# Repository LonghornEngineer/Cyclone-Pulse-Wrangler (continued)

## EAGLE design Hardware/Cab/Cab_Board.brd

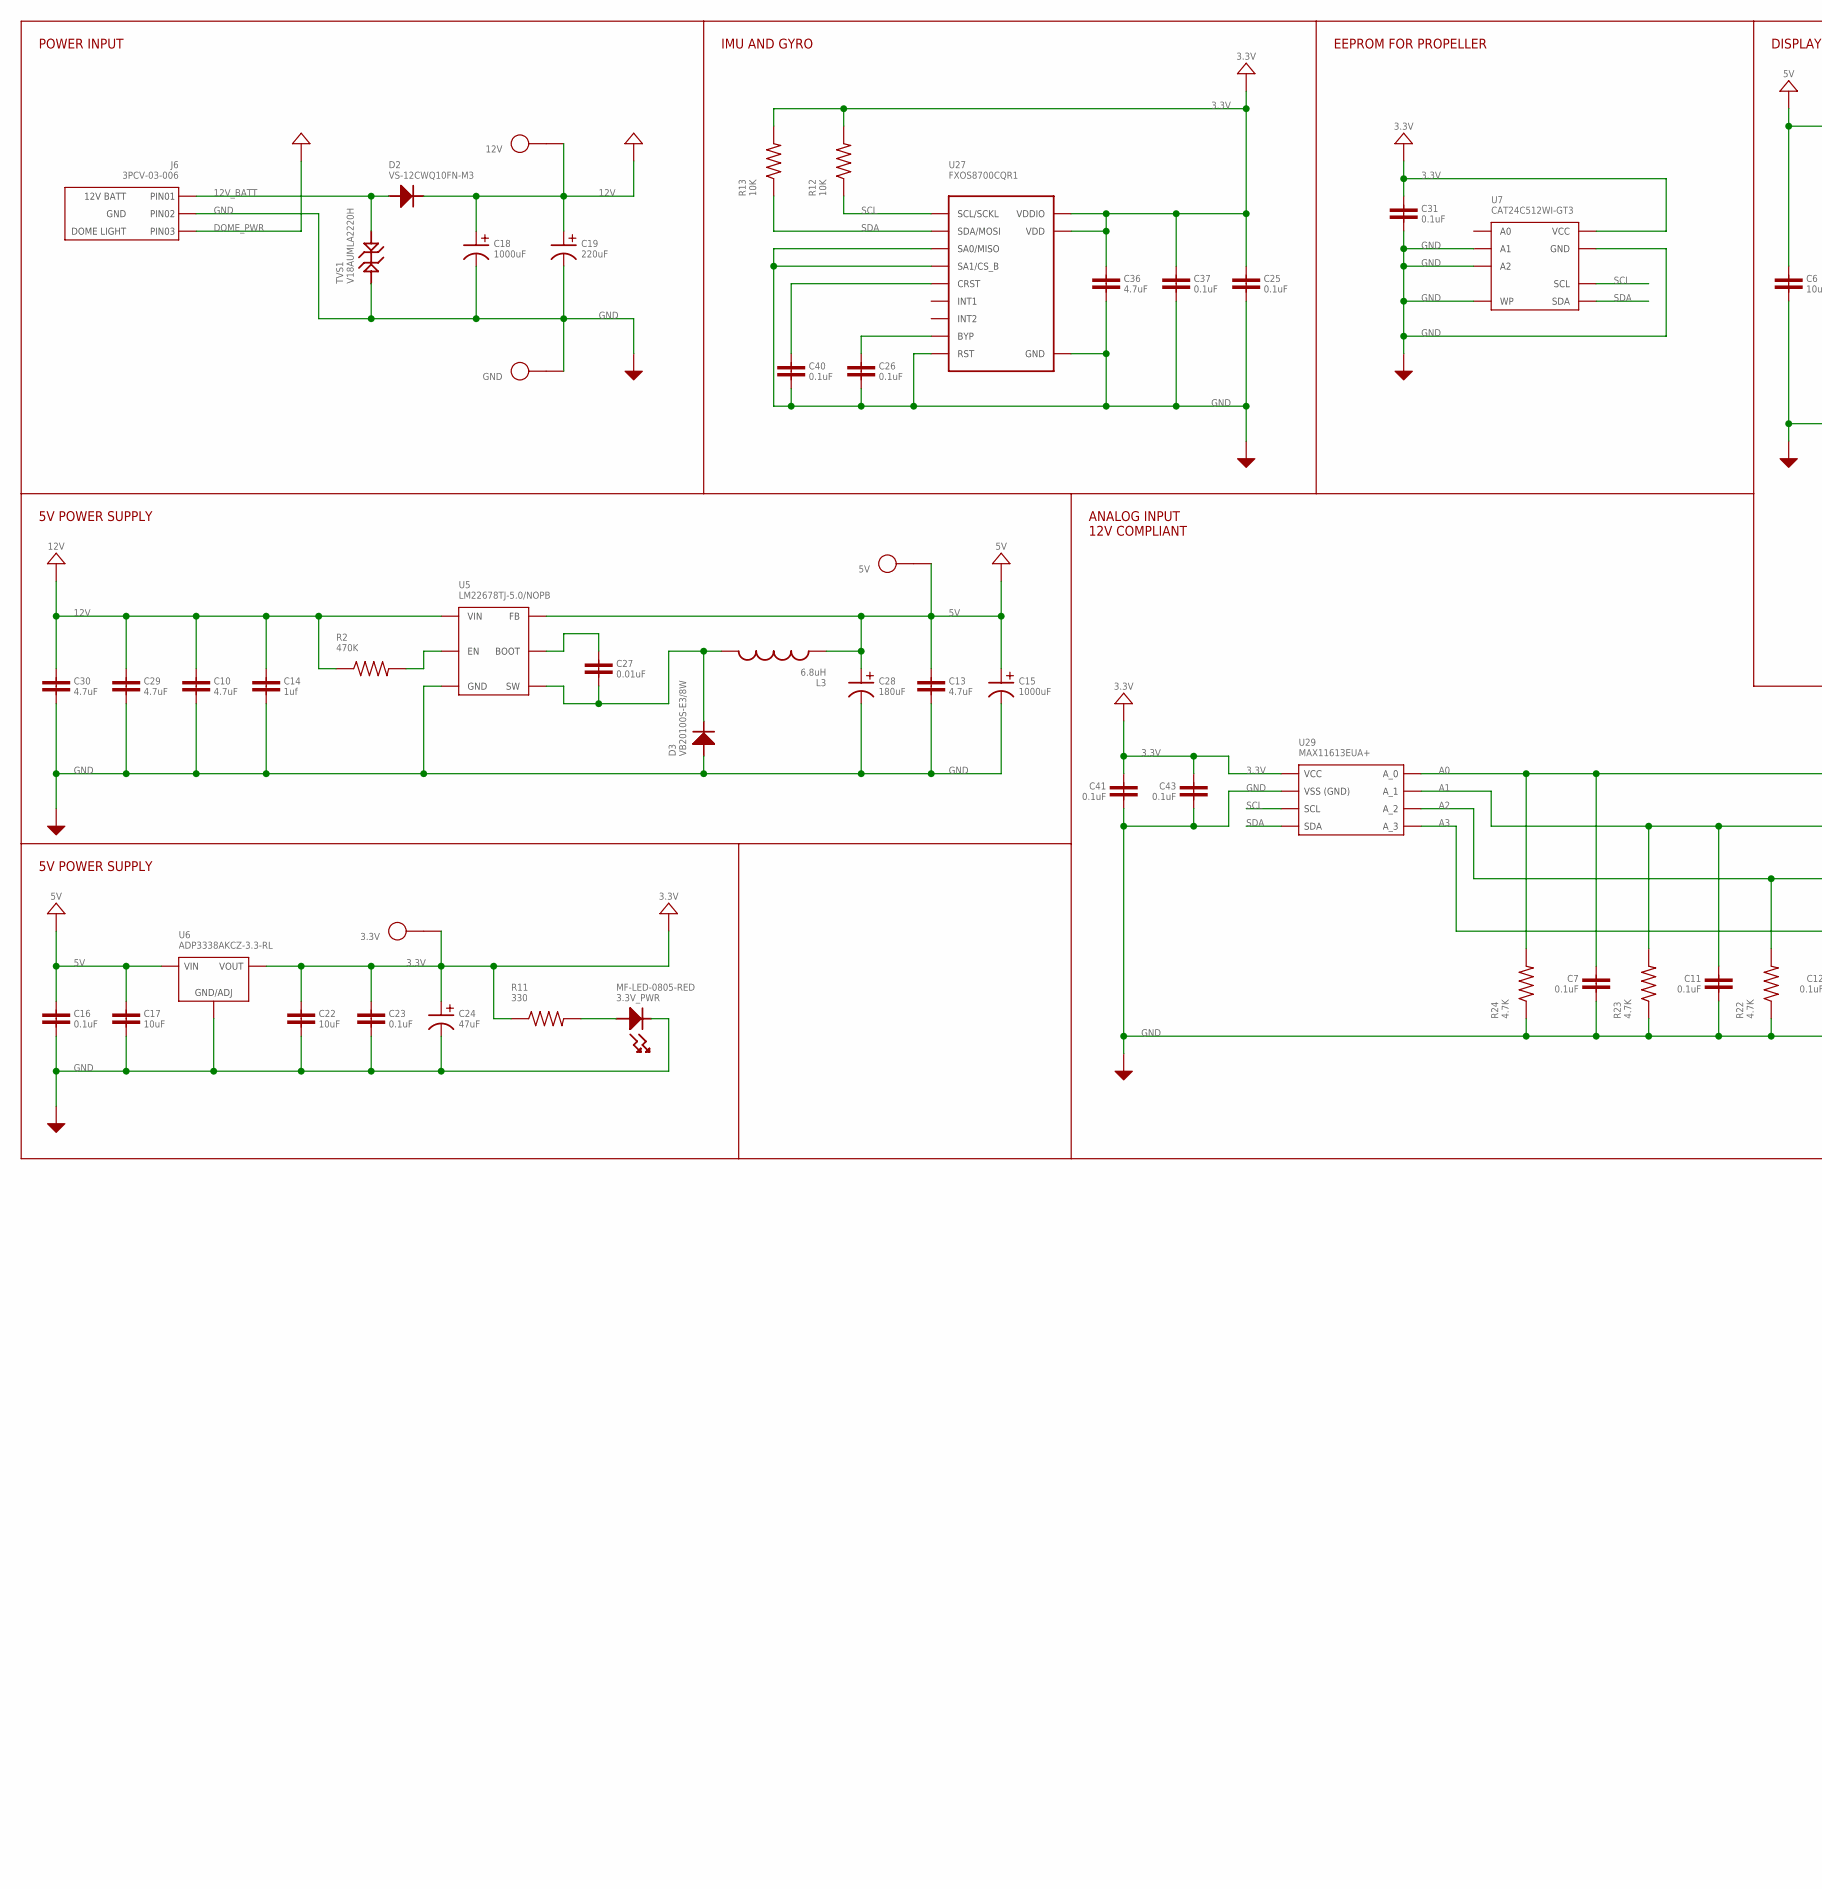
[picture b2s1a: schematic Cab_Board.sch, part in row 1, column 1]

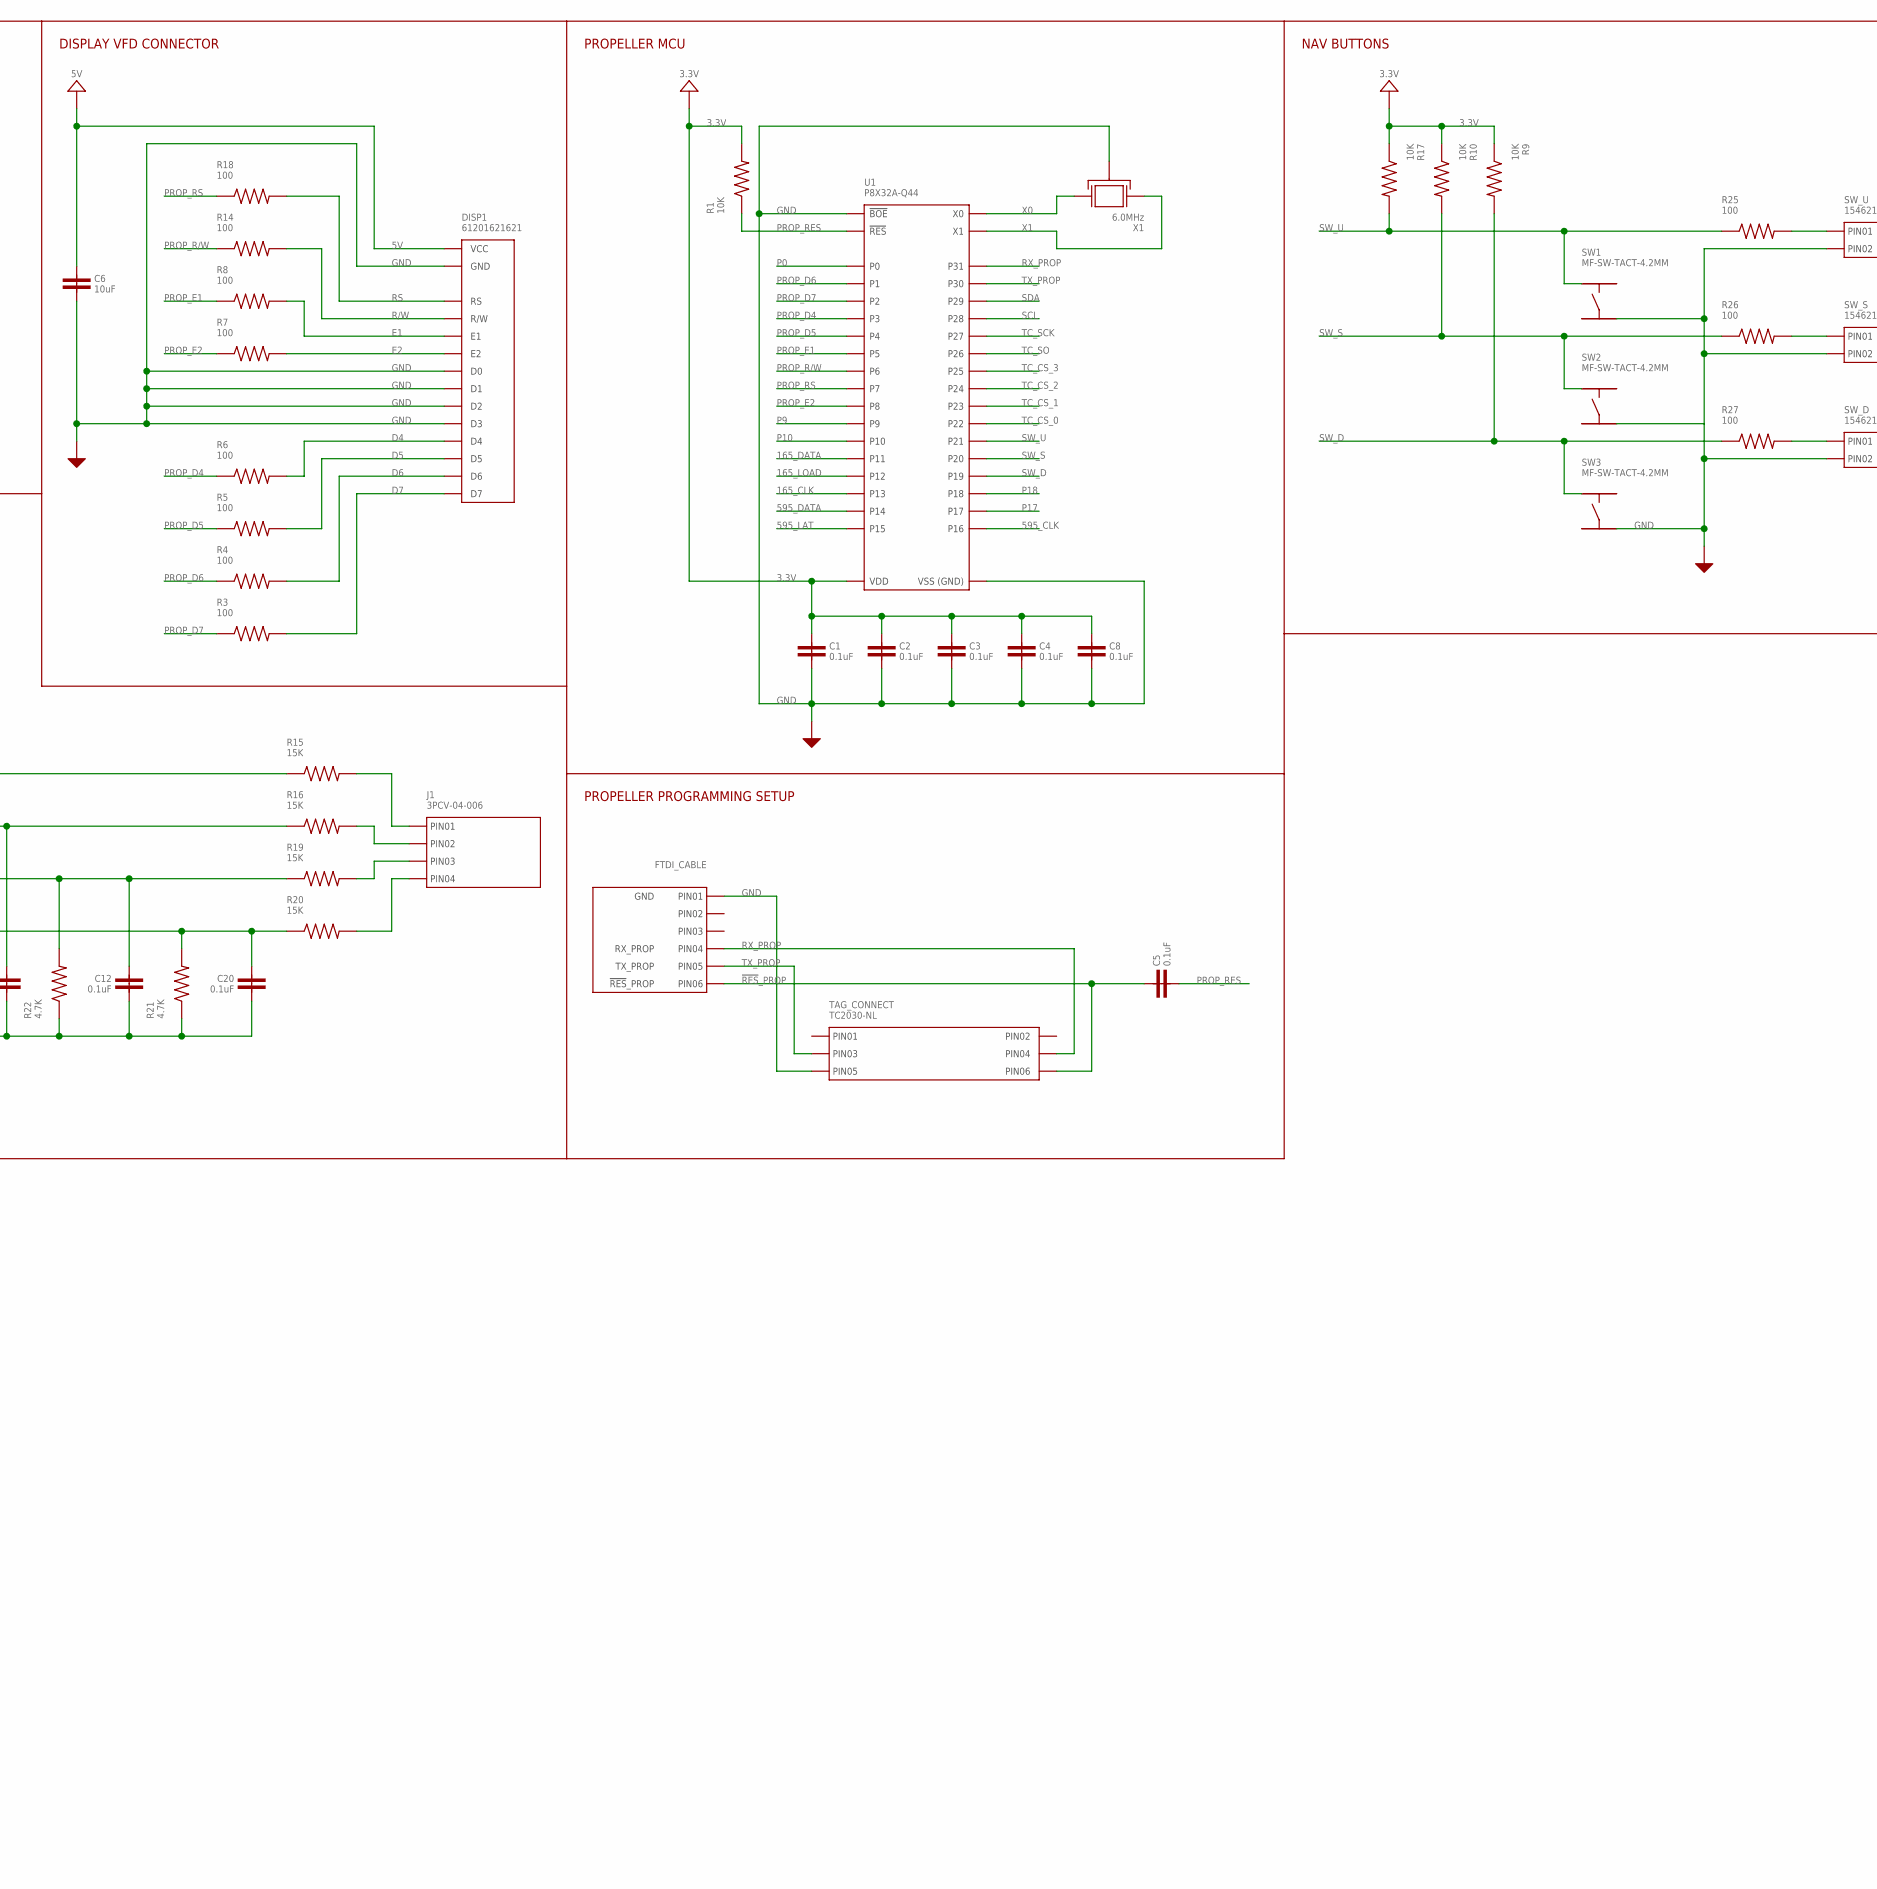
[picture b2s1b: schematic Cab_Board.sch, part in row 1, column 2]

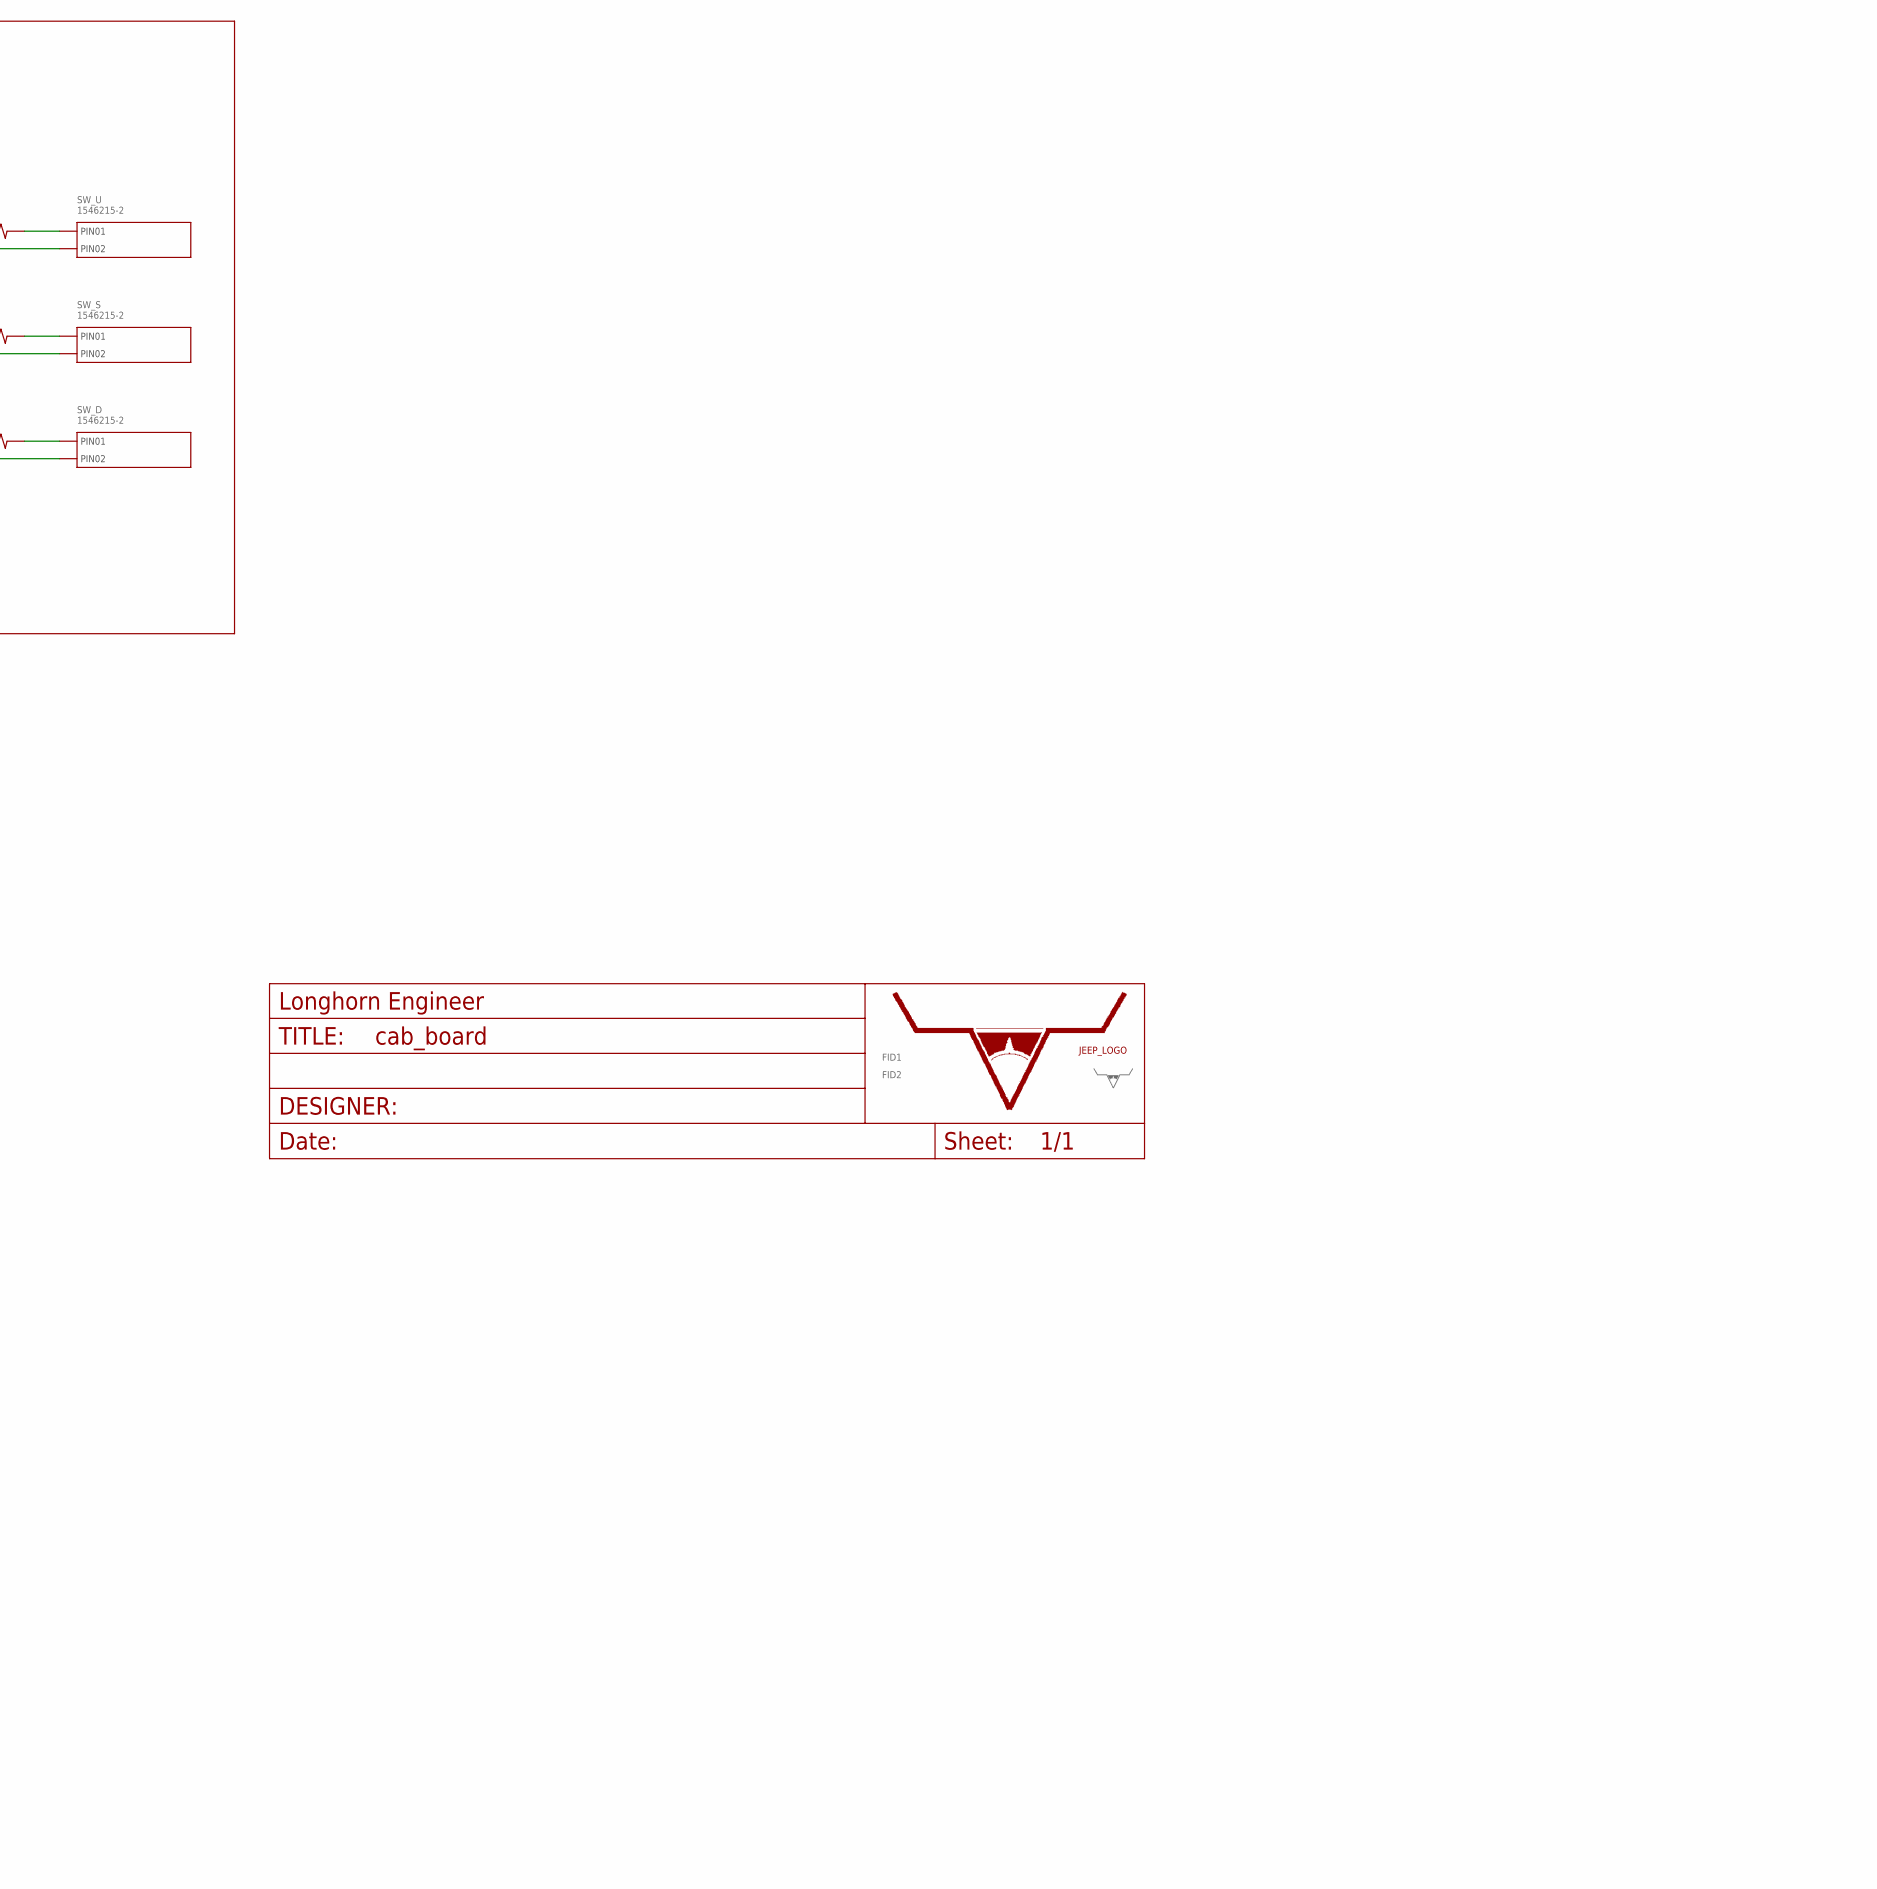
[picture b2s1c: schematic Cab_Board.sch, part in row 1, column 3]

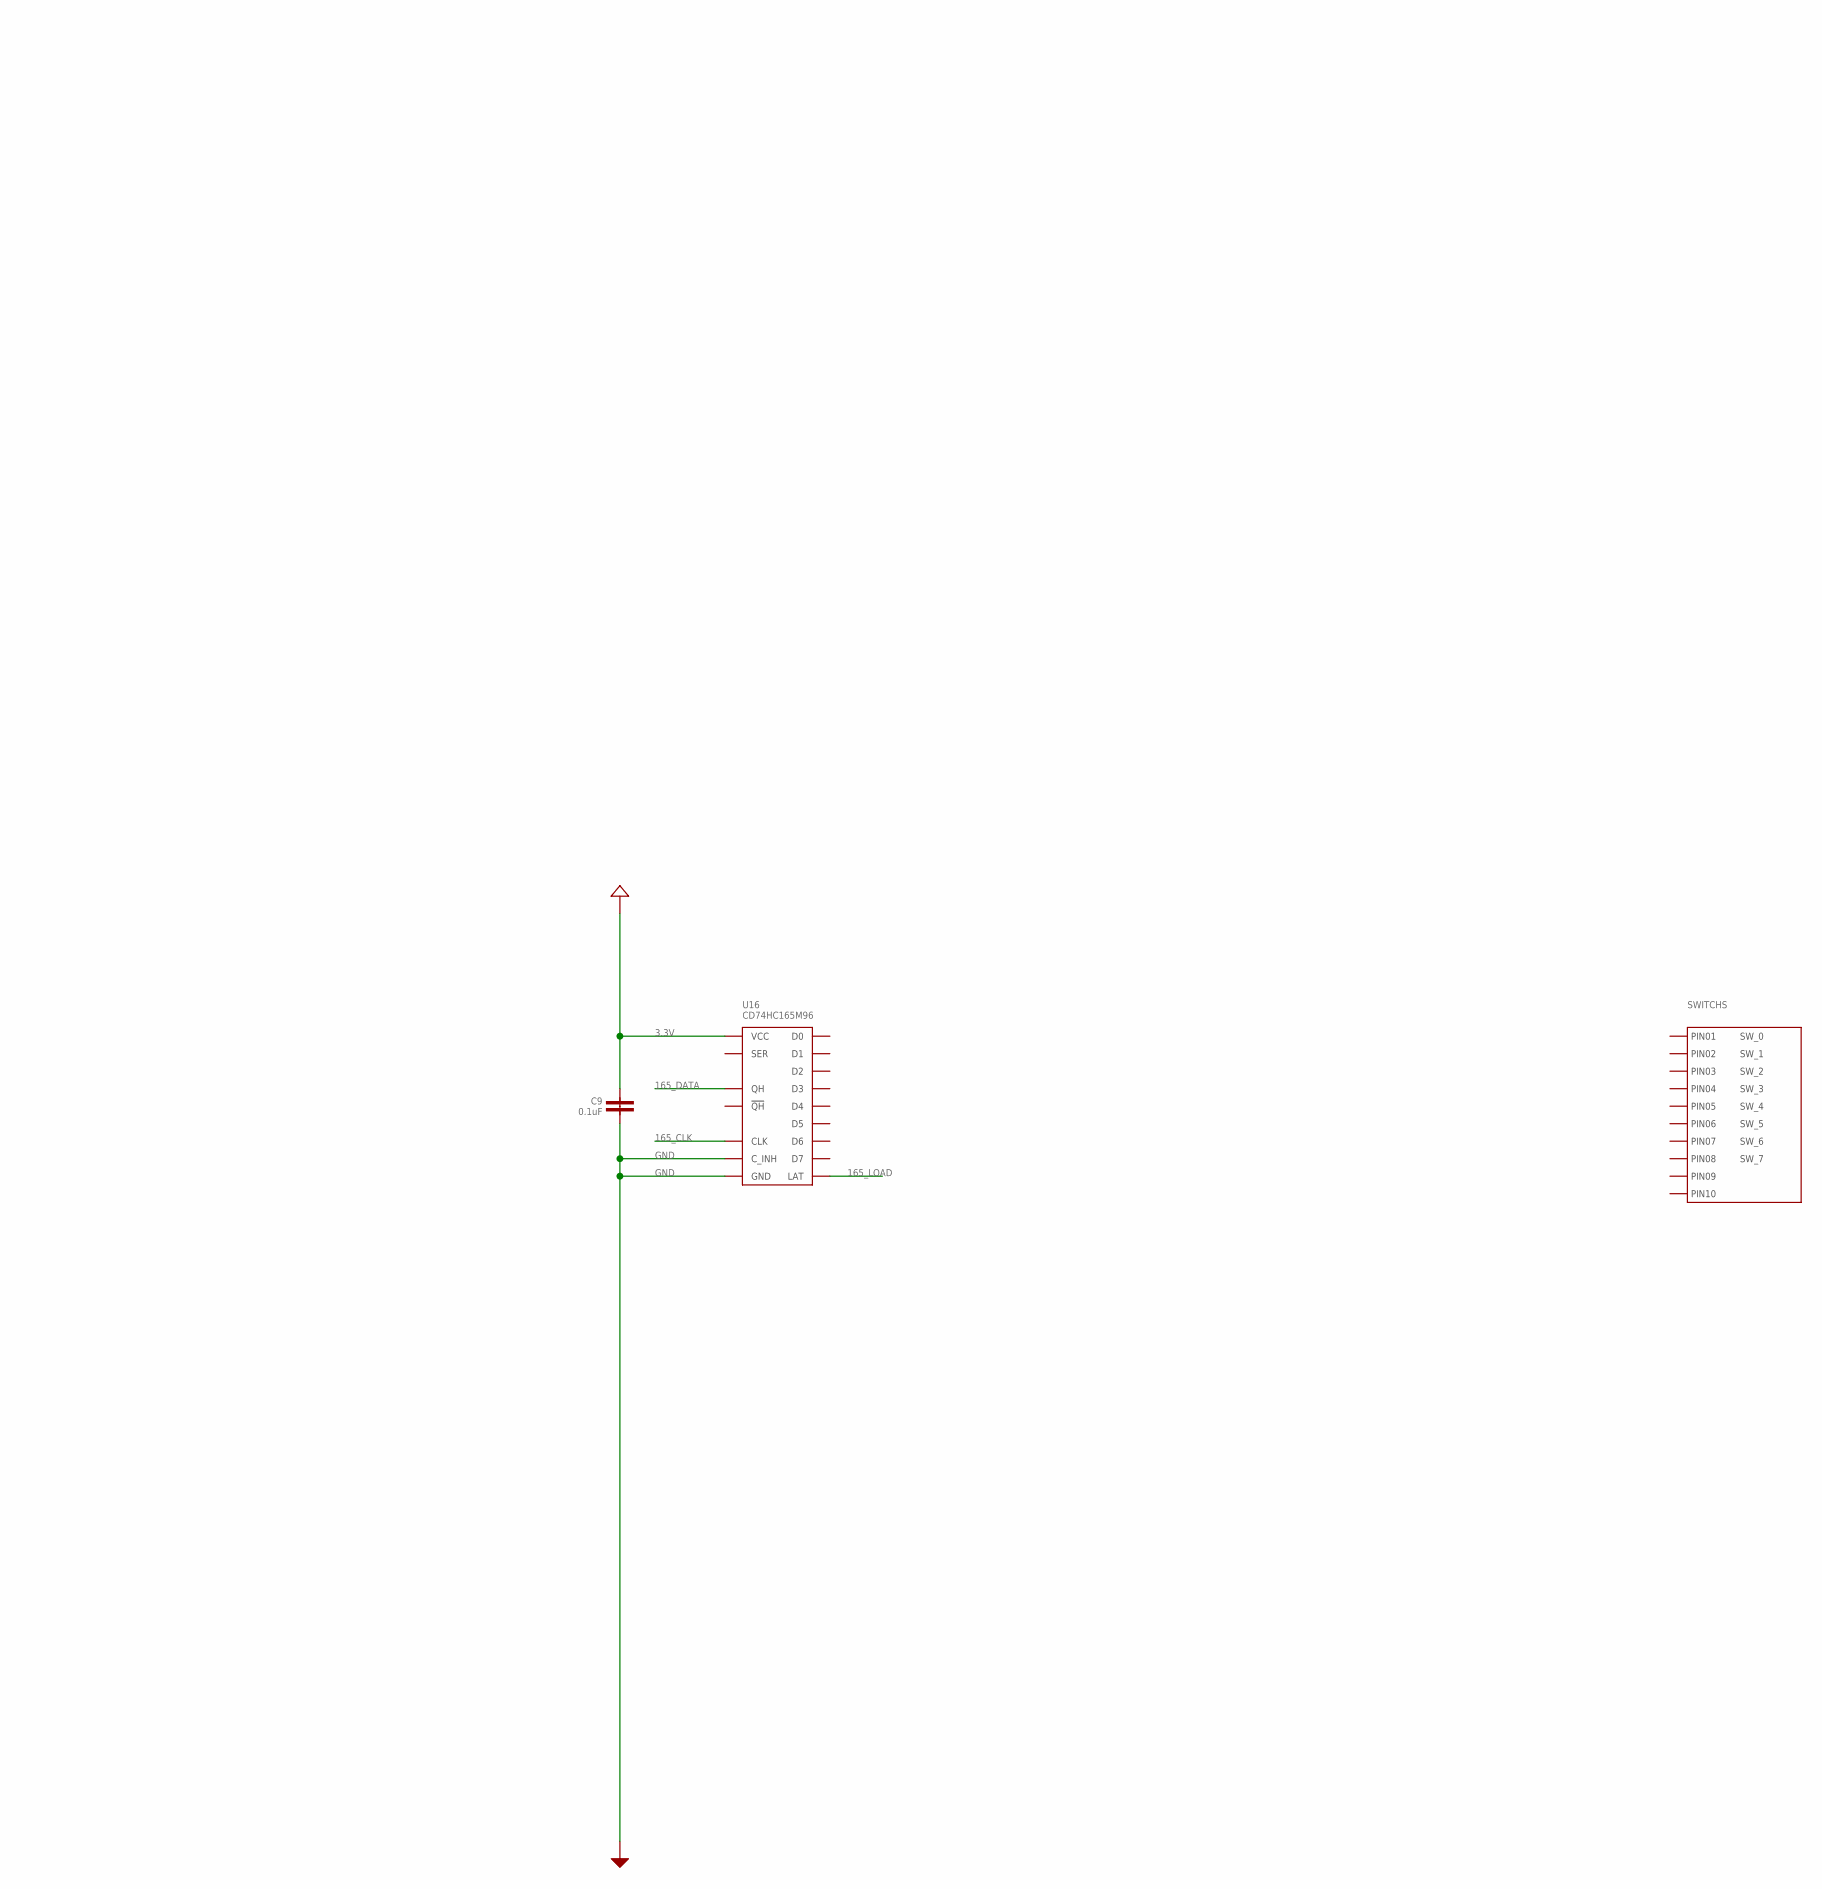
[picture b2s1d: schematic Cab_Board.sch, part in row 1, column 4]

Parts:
3.3V: TEST_POINT_SINGLE_KEYSTONE_5115-5119; KEYSTONE_5115-5119
3.3V_PWR: MF-LED-0805-RED; LED_0805; MPN MF-LED-0805-RED
5V, 12V: TEST_POINT_SINGLE_KEYSTONE_5115-5119; KEYSTONE_5115-5119; MPN 5115
C1, C2, C3, C4, C7, C8, C11, C12, C16, C20, C23, C25, C26, C31, C37, C40, C41, C43: 0.1uF; 0805; MPN MF-CAP-0805-0.1uF
C5: 0.1uF; 0603; MPN MF-CAP-0805-0.1uF
C6, C17: 10uF; 1206; MPN MF-CAP-1206-10uF
C9: 0.1uF; 0805
C10, C13, C29, C30: 4.7uF; 1210; MPN GRJ32DC72A475KE11L
C14: 1uf; 0805; MPN C0805C105K5RACTU
C15: 1000uF; 10MM_CAP_SMD; MPN UWZ1A102MCL1GS
C18: 1000uF; 12.5MM_CAP_PTH; MPN UBW1H102MHD
C19: 220uF; 10MM_CAP_SMD; MPN UWZ1H221MCL1GS
C22: 10uF; 1210; MPN MF-CAP-1206-10uF
C24: 47uF; 6.3MM_CAP_SMD; MPN UWJ1C470MCL1GB
C27: 0.01uF; 0805; MPN C0805C103K5RACTU
C28: 180uF; 8MM_CAP_SMD; MPN 16SVP180M
C36: 4.7uF; 1206; MPN GRJ32DC72A475KE11L
D2: VS-12CWQ10FN-M3; D-PAK(TO-252AA); MPN VS-12CWQ10FN-M3
D3: VB20100S-E3/8W; D2PAK(TO-263AB)
DISP1: 61201621621; CU40045-UW1J; MPN 61201621621
FID1, FID2: FIDUCIAL_0.5MM
FTDI_CABLE: CON_01X06_2.54MM_PIN_HEADER; 2.54MM_01X06_PIN_HEADER
GND: TEST_POINT_SINGLE_KEYSTONE_5115-5119; KEYSTONE_5115-5119; MPN 5115
J1: 3PCV-04-006; MPN 3PCV-04-006
J6: 3PCV-03-006; MPN 3PCV-03-006
L3: 6.8uH; IHLP-5050; MPN IHLP5050CEER6R8M01
R1: 10K; 0805
R2: 470K; 0603; MPN MF-RES-0603-470K
R3, R4, R5, R6, R7, R8, R14, R18, R25, R26, R27: 100; 0603; MPN MF-RES-0603-100
R9, R10, R12, R13, R17: 10K; 0603; MPN MF-RES-0603-10K
R11: 330; 0603; MPN MF-RES-0603-330
R15, R16, R19, R20: 15K; 0603; MPN MF-RES-0603-15K
R21, R22, R23, R24: 4.7K; 0603; MPN MF-RES-0603-4.7K
SW1, SW2, SW3: MF-SW-TACT-4.2MM; TACT4.2MM
SWITCHS: CON_01X10_1-282834-0; 1-282834-0
SW_D: 1546215-2; MPN 1546215-2
SW_S: 1546215-2; MPN 1546215-2
SW_U: 1546215-2; MPN 1546215-2
TAG_CONNECT: TC2030-NL; TC2030
TVS1: V18AUMLA2220H; 2220
U1: P8X32A-Q44; LQFP44
U5: LM22678TJ-5.0/NOPB; LM22678_TO-263-EP-7; MPN LM22678TJ-5.0/NOPB
U6: ADP3338AKCZ-3.3-RL; ADP3338_SOT-223-3; MPN ADP3338AKCZ-3.3-RL
U7: CAT24C512WI-GT3; SOIC-8_W; MPN CAT24C512WI-GT3
U16: CD74HC165M96; CD74HC165_SOIC-16
U27: FXOS8700CQR1; MPN FXOS8700CQR1
U29: MAX11613EUA+; MAX11613_UMAX-8; MPN MAX11613EUA+
U$1: LHE_FRAME
U$35: JEEP_LOGO_SILK_MEDIUM; JEEP_SILK_MEDIUM
U$42: LHE_LOGOLHE_LOGO; LHE_LOGO
X1: 6.0MHz; 7MMX5MM; MPN ABMM-6.000MHZ-B2-T

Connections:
3.3V: 3.3V.P$1, C1.1, C2.1, C3.1, C4.1, C8.1, C9.1, C22.1, C23.1, C24.POS, C25.1, C31.1, C36.1, C37.1, C41.1, C43.1, R1.2, R9.1, R10.1, R11.1, R12.2, R13.2, R17.1, U1.8 (VDD), U1.18 (VDD), U1.30 (VDD), U1.40 (VDD), U6.2 (OUT), U6.PAD (OUT), U7.8 (VCC), U16.16 (VCC), U27.P$1 (VDDIO), U27.P$14 (VDD), U29.P$8 (VCC)
5V: 5V.P$1, C6.1, C13.1, C15.POS, C16.1, C17.1, C28.POS, DISP1.P$13 (VCC), L3.1, U5.P$6 (FB), U6.3 (IN)
12V: 12V.P$1, C10.1, C14.1, C18.POS, C19.POS, C29.1, C30.1, D2.PAD-4 (CATHODE), R2.1, U5.P$2 (VIN)
12V_BATT: D2.1 (ANODE), D2.3 (ANODE), J6.1 (PIN1), TVS1.P$2
165_CLK: U1.14 (P13), U16.2 (CLK)
165_DATA: U1.12 (P11), U16.9 (QH)
165_LOAD: U1.13 (P12), U16.1 (LAT)
595_CLK: U1.19 (P16)
595_DATA: U1.15 (P14)
595_LAT: U1.16 (P15)
!RES!_PROP: C5.1, FTDI_CABLE.6, TAG_CONNECT.P$6 (PIN6)
A0: C7.1, R15.1, R24.2, U29.P$1 (A_0)
A1: C11.1, R16.1, R23.2, U29.P$2 (A_1)
A2: C12.1, R19.1, R22.2, U29.P$3 (A_2)
A3: C20.1, R20.1, R21.2, U29.P$4 (A_3)
D4: DISP1.P$3 (D4), R6.2
D5: DISP1.P$4 (D5), R5.2
D6: DISP1.P$1 (D6), R4.2
D7: DISP1.P$2 (D7), R3.2
DOME_PWR: J6.3 (PIN3)
E1: DISP1.P$10 (E1), R8.2
E2: DISP1.P$16 (E2), R7.2
GND: 3.3V_PWR.CATHODE, C1.2, C2.2, C3.2, C4.2, C6.2, C7.2, C8.2, C9.2, C10.2, C11.2, C12.2, C13.2, C14.2, C15.NEG, C16.2, C17.2, C18.NEG, C19.NEG, C20.2, C22.2, C23.2, C24.NEG, C25.2, C26.2, C28.NEG, C29.2, C30.2, C31.2, C36.2, C37.2, C40.2, C41.2, C43.2, D3.A (ANODE), DISP1.P$5 (D2), DISP1.P$6 (D3), DISP1.P$7 (D0), DISP1.P$8 (D1), DISP1.P$14 (GND), FTDI_CABLE.1, GND.P$1, J6.2 (PIN2), R21.1, R22.1, R23.1, R24.1, SW1.P$4, SW2.P$4, SW3.P$4, SW_D.P$2 (PIN2), SW_S.P$2 (PIN2), SW_U.P$2 (PIN2), TAG_CONNECT.P$5 (PIN5), TVS1.P$1, U1.5 (VSS), U1.6 (BOE'), U1.17 (VSS), U1.27 (VSS), U1.39 (VSS), U5.P$4 (GND), U5.PAD (GND), U6.1 (GND), U7.2 (A1), U7.3 (A2), U7.4 (GND), U7.7 (WP), U16.8 (GND), U16.15 (C_INH), U27.P$3 (GND), U27.P$5 (GND), U27.P$7 (SA0/MISO), U27.P$10 (SA1/CS_B), U27.P$12 (GND), U27.P$13 (GND), U27.P$16 (RST), U29.P$7 (GND), X1.P$2 (GND), X1.P$4 (GND)
unnamed: J1.1, R15.2
unnamed: C27.1, U5.P$3 (BOOT)
unnamed: J1.2, R16.2
unnamed: J1.3, R19.2
unnamed: C27.2, D3.C (CATHODE), L3.2, U5.P$1 (SW)
unnamed: J1.4, R20.2
unnamed: C26.1, U27.P$2 (BYP)
unnamed: C40.1, U27.P$8 (CRST)
unnamed: 3.3V_PWR.ANODE, R11.2
unnamed: R25.2, SW_U.P$1 (PIN1)
unnamed: R26.2, SW_S.P$1 (PIN1)
unnamed: R27.2, SW_D.P$1 (PIN1)
unnamed: R2.2, U5.P$7 (EN)
P0: U1.41 (P0)
P9: U1.10 (P9)
P10: U1.11 (P10)
P17: U1.20 (P17)
P18: U1.21 (P18)
PROP_D4: R6.1, U1.44 (P3)
PROP_D5: R5.1, U1.1 (P4)
PROP_D6: R4.1, U1.42 (P1)
PROP_D7: R3.1, U1.43 (P2)
PROP_E1: R8.1, U1.2 (P5)
PROP_E2: R7.1, U1.9 (P8)
PROP_R/W: R14.1, U1.3 (P6)
PROP_RES: C5.2, R1.1, U1.7 (RES')
PROP_RS: R18.1, U1.4 (P7)
R/W: DISP1.P$9 (R/W), R14.2
RS: DISP1.P$12 (RS), R18.2
RX_PROP: FTDI_CABLE.4, TAG_CONNECT.P$4 (PIN4), U1.38 (P31)
SCL: R12.1, U1.35 (P28), U7.6 (SCL), U27.P$4 (SCL/SCKL), U29.P$5 (SCL)
SDA: R13.1, U1.36 (P29), U7.5 (SDA), U27.P$6 (SDA/MOSI), U29.P$6 (SDA)
SW_D: R9.2, R27.1, SW3.P$1, U1.22 (P19)
SW_S: R10.2, R26.1, SW2.P$1, U1.23 (P20)
SW_U: R17.2, R25.1, SW1.P$1, U1.24 (P21)
TC_CS_0: U1.25 (P22)
TC_CS_1: U1.26 (P23)
TC_CS_2: U1.31 (P24)
TC_CS_3: U1.32 (P25)
TC_SCK: U1.34 (P27)
TC_SO: U1.33 (P26)
TX_PROP: FTDI_CABLE.5, TAG_CONNECT.P$3 (PIN3), U1.37 (P30)
X0: U1.29 (X0), X1.P$3 (X1)
X1: U1.28 (X1), X1.P$1 (X0)

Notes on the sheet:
POWER INPUT
5V POWER SUPPLY
IMU AND GYRO
EEPROM FOR PROPELLER
DISPLAY VFD CONNECTOR
ANALOG INPUT 12V COMPLIANT
PROPELLER MCU
PROPELLER PROGRAMMING SETUP
NAV BUTTONS

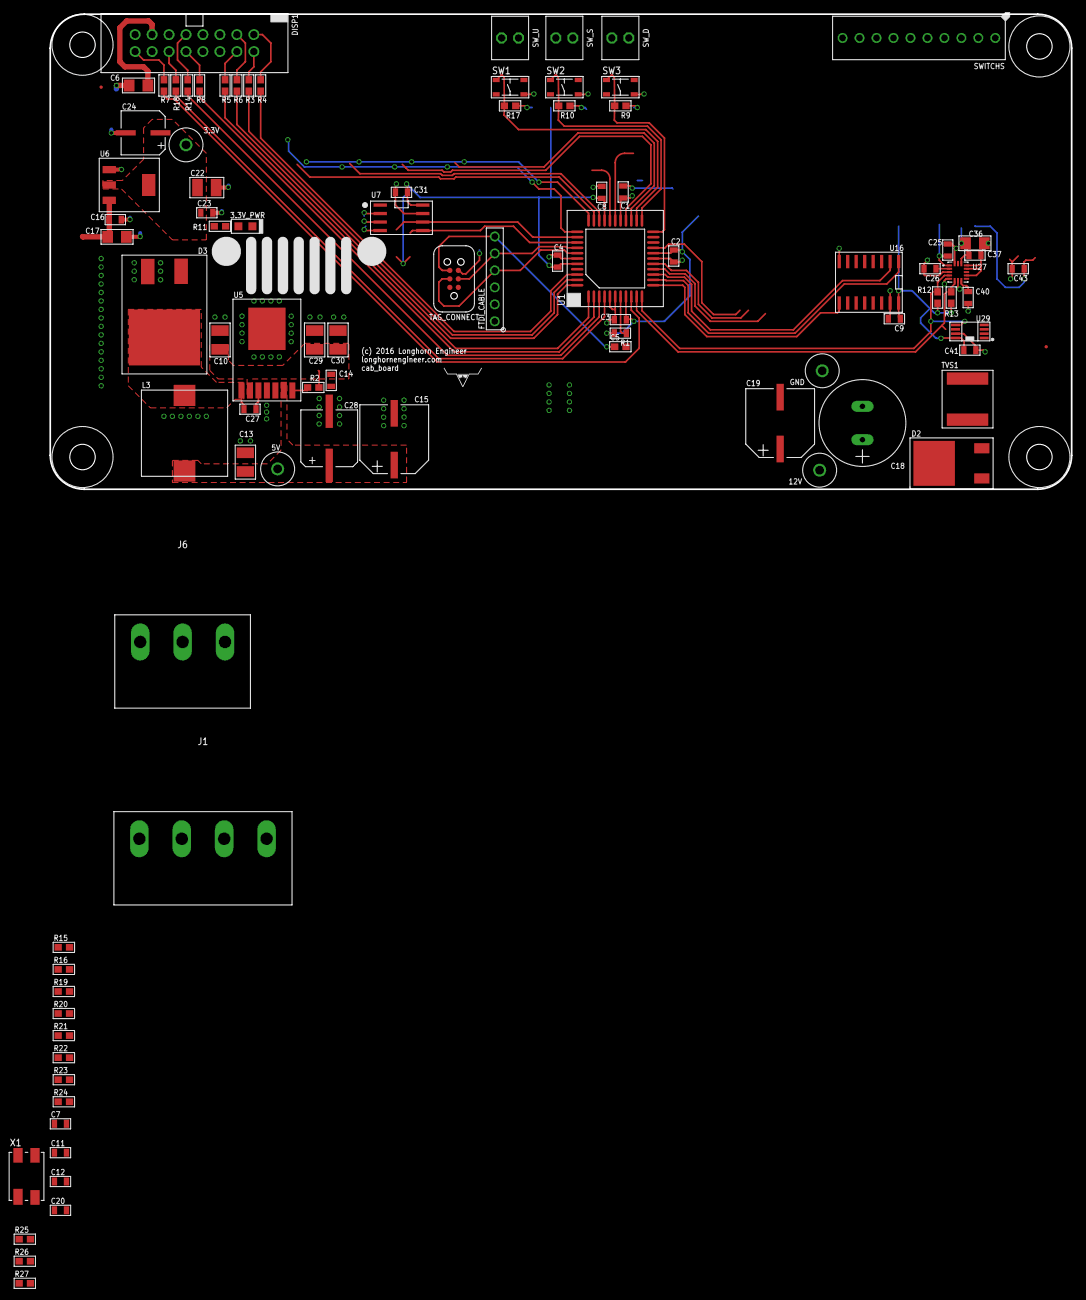
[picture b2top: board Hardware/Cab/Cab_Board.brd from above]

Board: 2 copper layers, 152.9 x 71.1 mm, 100 parts (0 on the bottom side), 52 nets.

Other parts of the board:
U$31, U$32, U$33, U$34: MOUNT_HOLE_150MIL
